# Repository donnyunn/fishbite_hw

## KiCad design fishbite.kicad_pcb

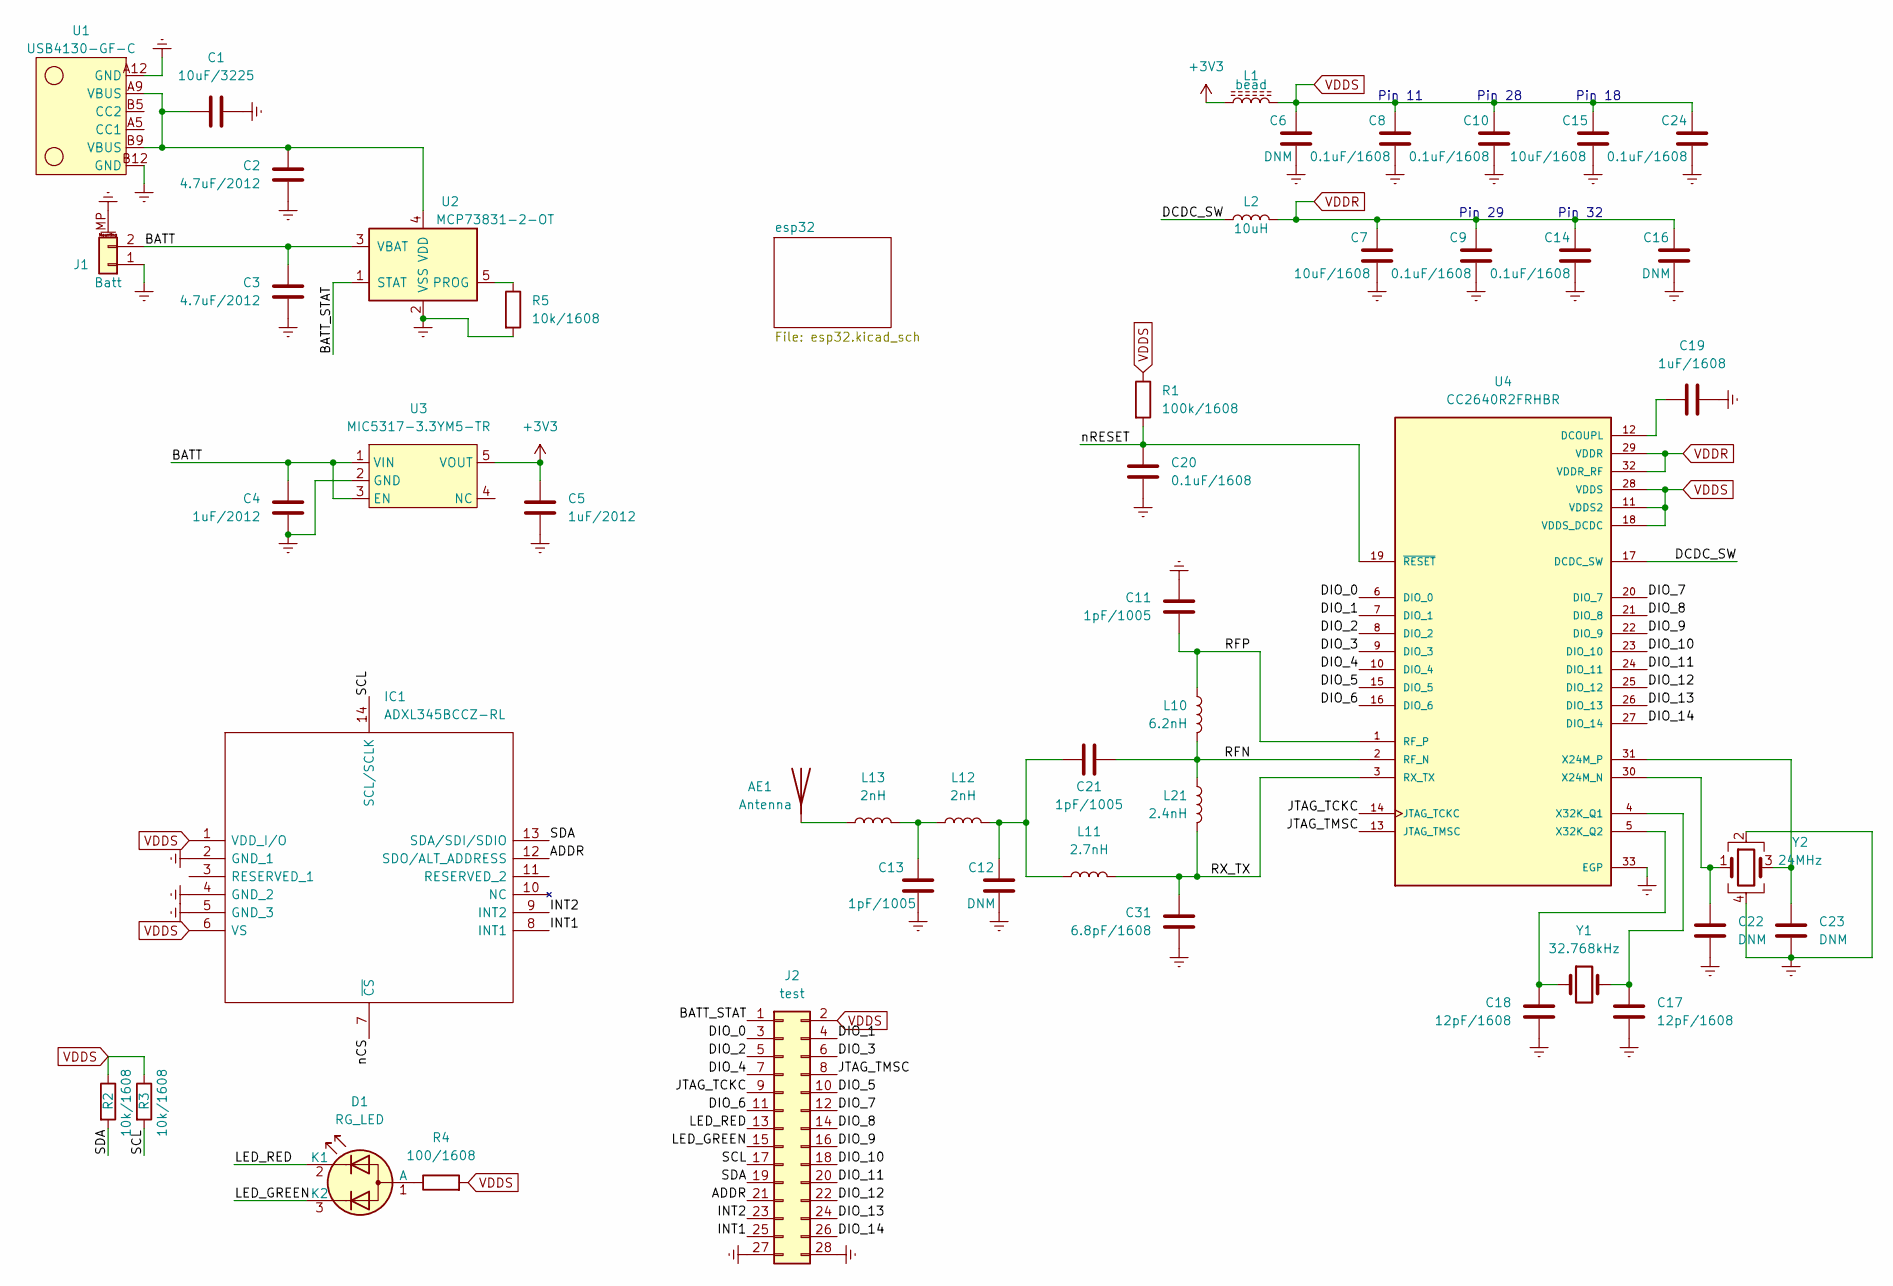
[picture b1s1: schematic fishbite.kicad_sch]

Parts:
AE1: Antenna; Texas_SWRA117D_2.4GHz_Right
C1: 10uF/3225; C_1210_3225Metric_Pad1.33x2.70mm_HandSolder; MPN CL32A106KOJNNNE
C2, C3: 4.7uF/2012; C_0805_2012Metric_Pad1.18x1.45mm_HandSolder; MPN CL21F475ZPFNNNE
C4, C5: 1uF/2012; C_0805_2012Metric_Pad1.18x1.45mm_HandSolder; MPN CL21B105KPFNNNE
C6, C12, C16, C22, C23: DNM; C_0603_1608Metric_Pad1.08x0.95mm_HandSolder
C7, C15: 10uF/1608; C_0603_1608Metric_Pad1.08x0.95mm_HandSolder; MPN CL10A106KQ8NNNL
C8, C9, C10, C14, C20, C24: 0.1uF/1608; C_0603_1608Metric_Pad1.08x0.95mm_HandSolder; MPN CL10B104KB8NNNC
C11, C13, C21: 1pF/1005; C_0402_1005Metric_Pad0.74x0.62mm_HandSolder; MPN CL05C010CB51PNC
C17, C18: 12pF/1608; C_0603_1608Metric_Pad1.08x0.95mm_HandSolder; MPN CL10C120JB81PNC
C19: 1uF/1608; C_0603_1608Metric_Pad1.08x0.95mm_HandSolder; MPN CL10B105KA8NNNC
C31: 6.8pF/1608; C_0603_1608Metric_Pad1.08x0.95mm_HandSolder; MPN CL10C6R8CB8NNNC
D1: RG_LED; APBA3010SURKCGKC-GX
IC1: ADXL345BCCZ-RL; ADXL345BCCZRL; Mouser Part Number 584-ADXL345BCCZ-R
J1: Batt; Molex_PicoBlade_53261-0271_1x02-1MP_P1.25mm_Horizontal; MPN 53261-0271
J2: test; PinHeader_2x14_P2.54mm_Vertical
L1: bead; L_0805_2012Metric_Pad1.05x1.20mm_HandSolder; MPN 742792097
L2: 10uH; L_1210_3225Metric_Pad1.42x2.65mm_HandSolder; MPN CBC3225T100KR
L10: 6.2nH; L_0603_1608Metric_Pad1.05x0.95mm_HandSolder
L11: 2.7nH; L_0603_1608Metric_Pad1.05x0.95mm_HandSolder
L12, L13: 2nH; L_0603_1608Metric_Pad1.05x0.95mm_HandSolder
L21: 2.4nH; L_0603_1608Metric_Pad1.05x0.95mm_HandSolder
R1: 100k/1608; R_0603_1608Metric_Pad0.98x0.95mm_HandSolder; MPN RC0603JR-07100KL
R2, R3, R5: 10k/1608; R_0603_1608Metric_Pad0.98x0.95mm_HandSolder; MPN RC0603JR-0710KL
R4: 100/1608; R_0603_1608Metric_Pad0.98x0.95mm_HandSolder; MPN RC0603FR-07100RL
U1: USB4130-GF-C; MPN USB4130-GF-C
U2: MCP73831-2-OT; SOT-23-5; MPN MCP73831T-2ACI/OT
U3: MIC5317-3.3YM5-TR; SOT95P280X145-5N; MPN MIC5317-3.3YM5-TR
U4: CC2640R2FRHBR; VQFN-32-1EP_5x5mm_P0.5mm_EP3.1x3.1mm; PARTREV C
Y1: 32.768kHz; Crystal_SMD_MicroCrystal_CM9V-T1A-2Pin_1.6x1.0mm_HandSolder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; MPN ECS-.327-12.5-16-TR3
Y2: 24MHz; Oscillator_SMD_Abracon_ASE-4Pin_3.2x2.5mm_HandSoldering; MPN ABM8-24.000MHZ-B2-T3

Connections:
+3V3: C5.1, L1.1, U3.5 (VOUT)
/ADDR: IC1.12 (SDO/ALT_ADDRESS), J2.21
/BATT: C3.2, C4.2, J1.2, U2.3 (VBAT), U3.1 (VIN), U3.3 (EN)
/BATT_STAT: J2.1, U2.1 (STAT)
/DCDC_SW: L2.1, U4.17 (DCDC_SW)
/DIO_0: J2.3, U4.6 (DIO_0)
/DIO_1: J2.4, U4.7 (DIO_1)
/DIO_2: J2.5, U4.8 (DIO_2)
/DIO_3: J2.6, U4.9 (DIO_3)
/DIO_4: J2.7, U4.10 (DIO_4)
/DIO_5: J2.10, U4.15 (DIO_5)
/DIO_6: J2.11, U4.16 (DIO_6)
/DIO_7: J2.12, U4.20 (DIO_7)
/DIO_8: J2.14, U4.21 (DIO_8)
/DIO_9: J2.16, U4.22 (DIO_9)
/DIO_10: J2.18, U4.23 (DIO_10)
/DIO_11: J2.20, U4.24 (DIO_11)
/DIO_12: J2.22, U4.25 (DIO_12)
/DIO_13: J2.24, U4.26 (DIO_13)
/DIO_14: J2.26, U4.27 (DIO_14)
/INT1: IC1.8 (INT1), J2.25
/INT2: IC1.9 (INT2), J2.23
/JTAG_TCKC: J2.9, U4.14 (JTAG_TCKC)
/JTAG_TMSC: J2.8, U4.13 (JTAG_TMSC)
/LED_GREEN: D1.3 (K2), J2.15
/LED_RED: D1.2 (K1), J2.13
/RFN: C21.1, L10.1, L21.2, U4.2 (RF_N)
/RFP: C11.1, L10.2, U4.1 (RF_P)
/RX_TX: C31.2, L11.1, L21.1, U4.3 (RX_TX)
/SCL: IC1.14 (SCL/SCLK), J2.17, R3.2
/SDA: IC1.13 (SDA/SDI/SDIO), J2.19, R2.2
/nCS: IC1.7 (~CS)
/nRESET: C20.2, R1.2, U4.19 (~RESET)
Earth: C1.1, C2.1, C3.1, C4.1, C5.2, C6.1, C7.1, C8.1, C9.1, C10.1, C11.2, C12.1, C13.1, C14.1, C15.1, C16.1, C17.2, C18.1, C19.1, C20.1, C22.2, C23.2, C24.1, C31.1, IC1.2 (GND_1), IC1.4 (GND_2), IC1.5 (GND_3), J1.1, J1.MP (MountPin), J2.27, J2.28, R5.2, U1.A12 (GND), U1.B12 (GND), U2.2 (VSS), U3.2 (GND), U4.33 (EGP), Y2.2, Y2.4; also elsewhere on the board
unnamed: AE1.1 (A), L13.2
unnamed: C1.2, C2.2, U1.A9 (VBUS), U1.B9 (VBUS), U2.4 (VDD)
unnamed: C12.2, C21.2, L11.2, L12.1
unnamed: C13.2, L12.2, L13.1
unnamed: C17.1, U4.4 (X32K_Q1), Y1.2
unnamed: C18.2, U4.5 (X32K_Q2), Y1.1
unnamed: C19.2, U4.12 (DCOUPL)
unnamed: C22.1, U4.30 (X24M_N), Y2.1
unnamed: C23.1, U4.31 (X24M_P), Y2.3
unnamed: D1.1 (A), R4.1
unnamed: R5.1, U2.5 (PROG)
VDDR: C7.2, C9.2, C14.2, C16.2, L2.2, U4.29 (VDDR), U4.32 (VDDR_RF)
VDDS: C6.2, C8.2, C10.2, C15.2, C24.2, IC1.1 (VDD_I/O), IC1.6 (VS), J2.2, L1.2, R1.1, R2.1, R3.1, R4.2, U4.11 (VDDS2), U4.18 (VDDS_DCDC), U4.28 (VDDS)

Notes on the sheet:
Pin 18
Pin 29
Pin 11
Pin 28
Pin 32

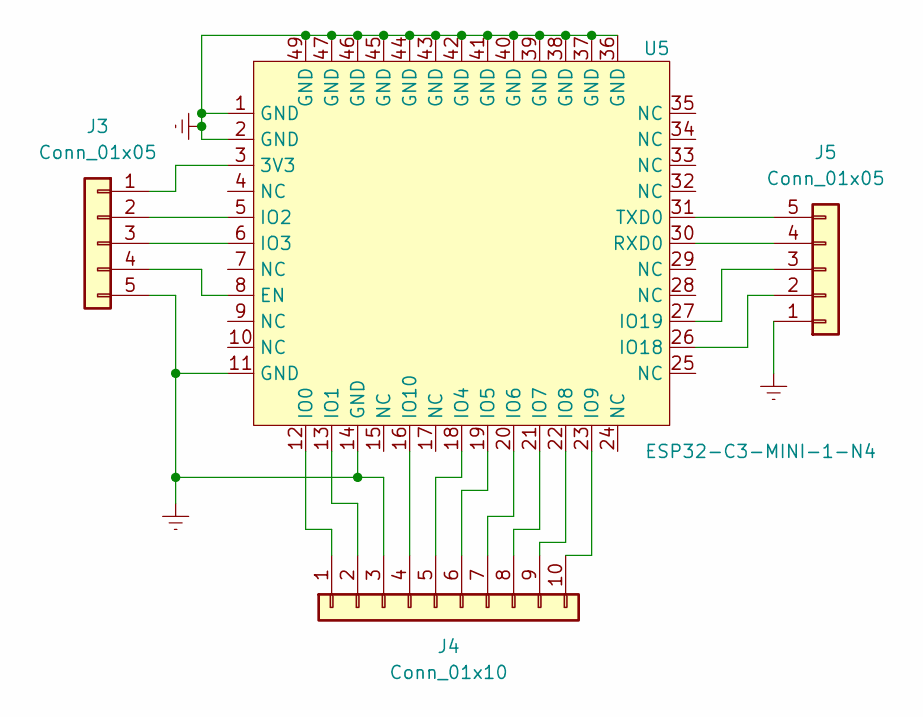
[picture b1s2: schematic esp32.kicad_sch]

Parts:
J3, J5: Conn_01x05; PinHeader_1x05_P2.54mm_Vertical
J4: Conn_01x10; PinHeader_1x10_P2.54mm_Vertical
U5: ESP32-C3-MINI-1-N4; ESP32-C4-MINI-1

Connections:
Earth: J3.5, J4.3, J5.1, U5.1 (GND), U5.2 (GND), U5.11 (GND), U5.14 (GND), U5.36 (GND), U5.37 (GND), U5.38 (GND), U5.39 (GND), U5.40 (GND), U5.41 (GND), U5.42 (GND), U5.43 (GND), U5.44 (GND), U5.45 (GND), U5.46 (GND), U5.47 (GND), U5.48 (GND), U5.49 (GND), U5.50 (GND), U5.51 (GND), U5.52 (GND), U5.53 (GND); also elsewhere on the board
unnamed: J3.1, U5.3 (3V3)
unnamed: J3.2, U5.5 (IO2)
unnamed: J3.3, U5.6 (IO3)
unnamed: J3.4, U5.8 (EN)
unnamed: J4.1, U5.12 (IO0)
unnamed: J4.2, U5.13 (IO1)
unnamed: J4.4, U5.16 (IO10)
unnamed: J4.5, U5.18 (IO4)
unnamed: J4.6, U5.19 (IO5)
unnamed: J4.7, U5.20 (IO6)
unnamed: J4.8, U5.21 (IO7)
unnamed: J4.9, U5.22 (IO8)
unnamed: J4.10, U5.23 (IO9)
unnamed: J5.2, U5.26 (IO18)
unnamed: J5.3, U5.27 (IO19)
unnamed: J5.4, U5.30 (RXD0)
unnamed: J5.5, U5.31 (TXD0)

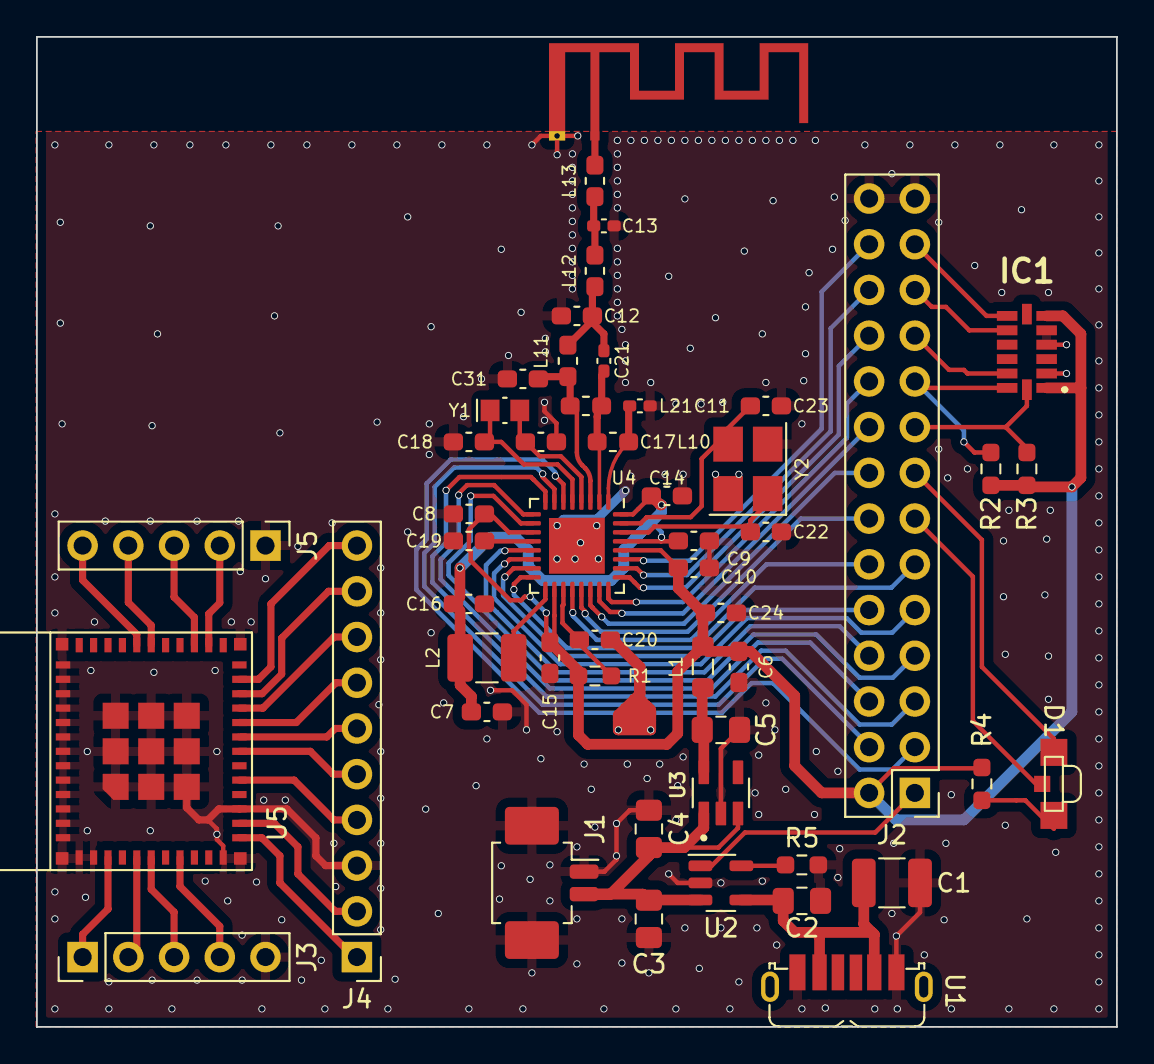
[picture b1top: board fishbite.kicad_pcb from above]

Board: 2 copper layers, 60.0 x 55.0 mm, 52 parts (0 on the bottom side), 63 nets.

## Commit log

2022-06-09 generate kicad project
2022-06-09 2022-06-09
2022-06-13 2022-06-13
2022-06-14 2022-06-14
2022-06-15 2022-06-14 2
2022-06-17 2022-06-17
2022-06-20 2022-06-20
2022-07-18 2022-07-18
2022-07-18 gitignore modified
